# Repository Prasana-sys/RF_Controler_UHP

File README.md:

# RF_Controler_UHP

Controller Firmware - Contains STM32 code files

STM_RF_PCB - Contains PCB files

Documents - Documents used to build this project

old_RFST - old PCB design

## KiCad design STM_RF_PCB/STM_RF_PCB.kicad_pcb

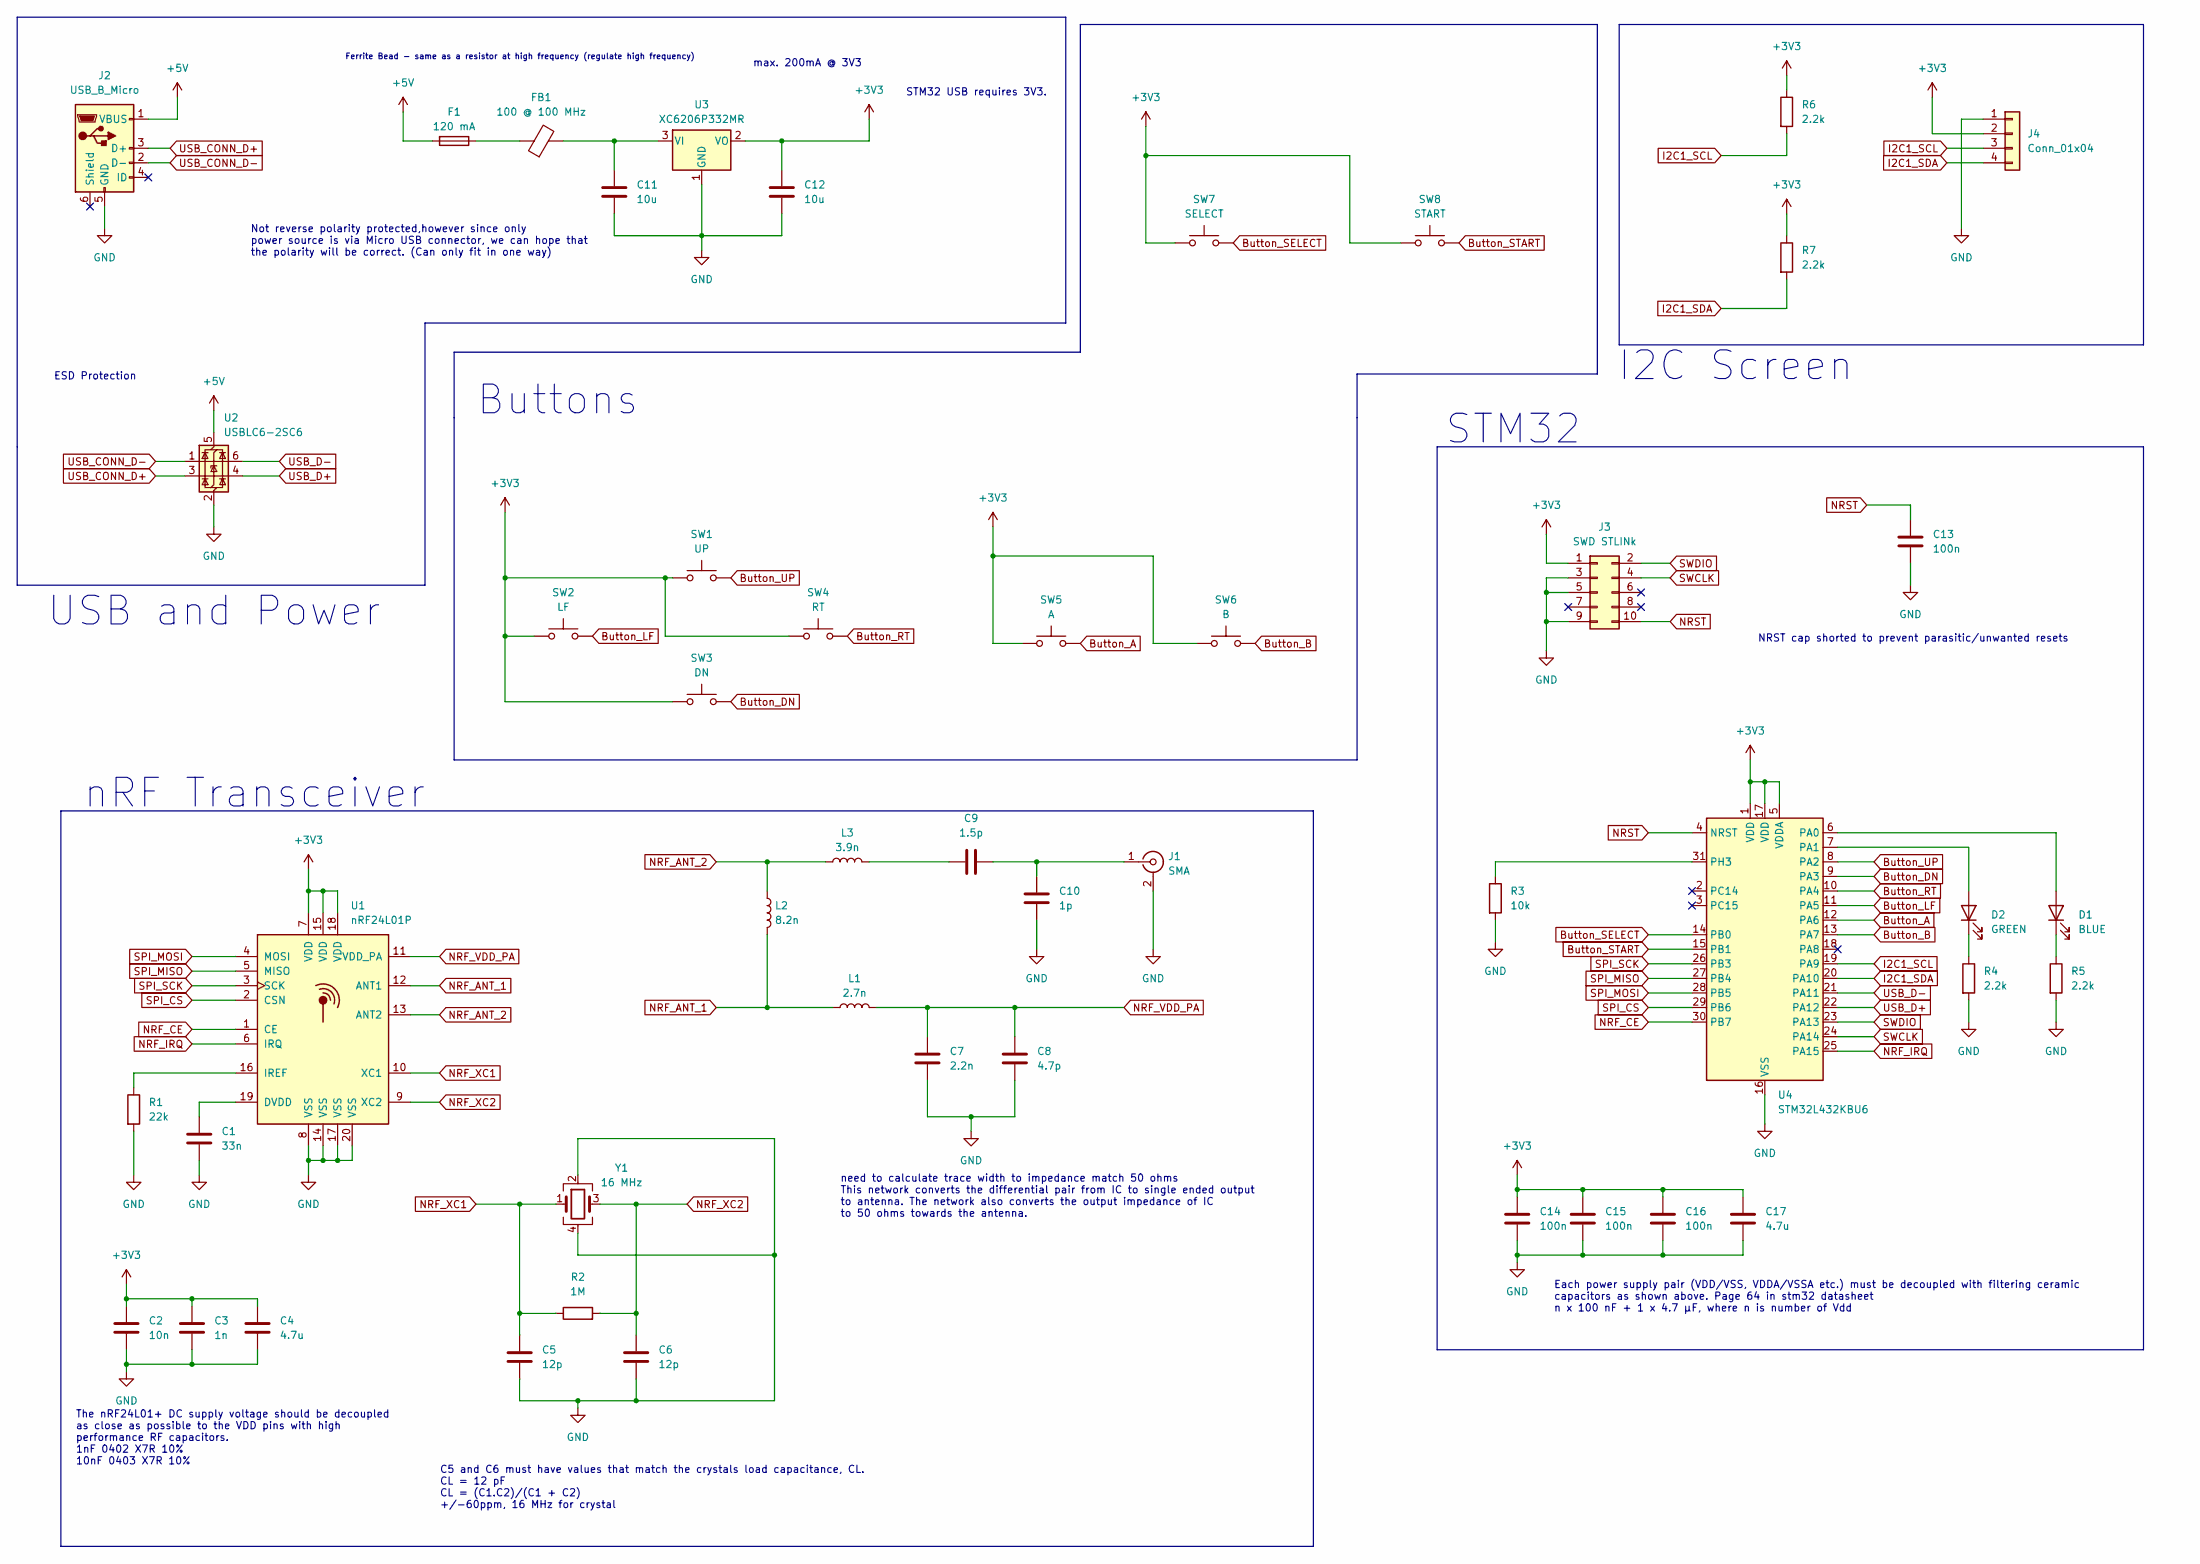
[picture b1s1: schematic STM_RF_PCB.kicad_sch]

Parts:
C1: 33n; C_0402_1005Metric; Part ID 0402F333M500NT
C2: 10n; R_0603_1608Metric; Part ID 0603B103K101NT
C3: 1n; C_0402_1005Metric; Part ID CC0402KRX7R7BB102
C4, C17: 4.7u; C_0603_1608Metric; Part ID CL10A475KP8NNNC
C5, C6: 12p; C_0402_1005Metric; Part ID 0402CG120J500NT
C7: 2.2n; C_0402_1005Metric; Part ID 0402B222K500NT
C8: 4.7p; C_0402_1005Metric; Part ID 0402CG4R7C500NT
C9: 1.5p; C_0402_1005Metric; Part ID 0402CG1R5C500NT
C10: 1p; C_0402_1005Metric; Part ID 0402CG1R0C500NT
C11, C12: 10u; C_0603_1608Metric; Part ID CL10A106KP8NNNC
C13, C14, C15, C16: 100n; C_0402_1005Metric; Part ID CL05B104KO5NNNC
D1: BLUE; LED_0603_1608Metric; Part ID 19-213/Y2C-CQ2R2L/3T(CY)
D2: GREEN; LED_0603_1608Metric; Part ID 19-217/GHC-YN1P2B18X/6T
F1: 120 mA; Fuse_1206_3216Metric; Part ID nSMD012
FB1: 100 @ 100 MHz; L_0805_2012Metric; Part ID GZ2012D101TF
J1: SMA; SMA-KWE902; Part ID SMA-KWE902
J2: USB_B_Micro; MICRO-02-G2P3-A1T2; Part ID MICRO-02-G2P3-A1T2
J3: SWD STLINk; PinHeader_2x05_P2.54mm_Vertical; Part ID HB-PH8-25425PB2GOP
J4: Conn_01x04; PinSocket_1x04_P2.54mm_Vertical; Part ID C2718488
L1: 2.7n; L_0402_1005Metric; Part ID SDCL1005C2N7STDF
L2: 8.2n; L_0402_1005Metric; Part ID SDCL1005C8N2JTDF
L3: 3.9n; L_0402_1005Metric; Part ID SDCL1005C3N9STDF
R1: 22k; R_0402_1005Metric; Part ID 0402WGF2202TCE
R2: 1M; R_0402_1005Metric; Part ID 0402WGF1004TCE
R3: 10k; R_0402_1005Metric; Part ID 0402WGF1002TCE
R4, R5, R6, R7: 2.2k; R_0603_1608Metric; Part ID 0603WAF2201T5E
SW1: UP; TC-1103-C-D; Part ID TC-1103-C-D
SW2: LF; TC-1103-C-D; Part ID TC-1103-C-D
SW3: DN; TC-1103-C-D; Part ID TC-1103-C-D
SW4: RT; TC-1103-C-D; Part ID TC-1103-C-D
SW5: A; TC-1103-C-D; Part ID TC-1103-C-D
SW6: B; TC-1103-C-D; Part ID TC-1103-C-D
SW7: SELECT; TC-1103-C-D; Part ID TC-1103-C-D
SW8: START; TC-1103-C-D; Part ID TC-1103-C-D
U1: nRF24L01P; QFN-20-1EP_4x4mm_P0.5mm_EP2.5x2.5mm
U2: USBLC6-2SC6; SOT-23-6
U3: XC6206P332MR
U4: STM32L432KBU6; Part ID C94784
Y1: 16 MHz; Crystal_SMD_3225-4Pin_3.2x2.5mm; Part ID X322516MLB4SI

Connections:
+3V3: C2.1, C3.1, C4.1, C12.1, C14.1, C15.1, C16.1, C17.1, J3.1, J4.2, R6.1, R7.1, SW1.1, SW2.1, SW3.1, SW4.1, SW5.1, SW6.1, SW7.1, SW8.1, U1.7 (VDD), U1.15 (VDD), U1.18 (VDD), U3.2 (VO), U4.1 (VDD), U4.5 (VDDA), U4.17 (VDD); also elsewhere on the board
+5V: F1.2, J2.1 (VBUS), U2.5 (VBUS)
Button_A: SW5.2, U4.12 (PA6)
Button_B: SW6.2, U4.13 (PA7)
Button_DN: SW3.2, U4.9 (PA3)
Button_LF: SW2.2, U4.11 (PA5)
Button_RT: SW4.2, U4.10 (PA4)
Button_SELECT: SW7.2, U4.14 (PB0)
Button_START: SW8.2, U4.15 (PB1)
Button_UP: SW1.2, U4.8 (PA2)
GND: C1.2, C2.2, C3.2, C4.2, C5.2, C6.2, C7.2, C8.2, C10.2, C11.2, C12.2, C13.2, C14.2, C15.2, C16.2, C17.2, J1.2 (Ext), J2.5 (GND), J3.3, J3.5, J3.9, J4.1, R1.2, R3.2, R4.2, R5.2, U1.8 (VSS), U1.14 (VSS), U1.17 (VSS), U1.20 (VSS), U2.2 (GND), U3.1 (GND), U4.16 (VSS), U4.32 (VSS), U4.33 (VSS), Y1.2, Y1.4; also elsewhere on the board
I2C1_SCL: J4.3, R6.2, U4.19 (PA9)
I2C1_SDA: J4.4, R7.2, U4.20 (PA10)
NRF_ANT_1: L1.1, L2.2, U1.12 (ANT1)
NRF_ANT_2: L2.1, L3.1, U1.13 (ANT2)
NRF_CE: U1.1 (CE), U4.30 (PB7)
NRF_IRQ: U1.6 (IRQ), U4.25 (PA15)
NRF_VDD_PA: C7.1, C8.1, L1.2, U1.11 (VDD_PA)
NRF_XC1: C5.1, R2.1, U1.10 (XC1), Y1.1
NRF_XC2: C6.1, R2.2, U1.9 (XC2), Y1.3
NRST: C13.1, J3.10, U4.4 (NRST)
unnamed: C9.1, L3.2
unnamed: D1.2 (A), U4.6 (PA0)
unnamed: D1.1 (K), R5.1
unnamed: D2.2 (A), U4.7 (PA1)
unnamed: D2.1 (K), R4.1
unnamed: F1.1, FB1.1
unnamed: C9.2, C10.1, J1.1 (In)
unnamed: C1.1, U1.19 (DVDD)
unnamed: R1.1, U1.16 (IREF)
unnamed: C11.1, FB1.2, U3.3 (VI)
unnamed: R3.1, U4.31 (PH3)
SPI_CS: U1.2 (CSN), U4.29 (PB6)
SPI_MISO: U1.5 (MISO), U4.27 (PB4)
SPI_MOSI: U1.4 (MOSI), U4.28 (PB5)
SPI_SCK: U1.3 (SCK), U4.26 (PB3)
SWCLK: J3.4, U4.24 (PA14)
SWDIO: J3.2, U4.23 (PA13)
USB_CONN_D+: J2.3 (D+), U2.3 (I/O2)
USB_CONN_D-: J2.2 (D-), U2.1 (I/O1)
USB_D+: U2.4 (I/O2), U4.22 (PA12)
USB_D-: U2.6 (I/O1), U4.21 (PA11)

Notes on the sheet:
I2C Screen
Buttons
NRST cap shorted to prevent parasitic/unwanted resets
need to calculate trace width to impedance match 50 ohms This network converts the differential pair from IC to single ended output to antenna. The network also converts the output impedance of IC to 50 ohms towards the antenna.
The nRF24L01+ DC supply voltage should be decoupled as close as possible to the VDD pins with high performance RF capacitors. 1nF 0402 X7R 10% 10nF 0403 X7R 10%
nRF Transceiver
STM32
Each power supply pair (VDD/VSS, VDDA/VSSA etc.) must be decoupled with filtering ceramic capacitors as shown above. Page 64 in stm32 datasheet n x 100 nF + 1 x 4.7 μF, where n is number of Vdd
ESD Protection
Not reverse polarity protected,however since only power source is via Micro USB connector, we can hope that the polarity will be correct. (Can only fit in one way)
C5 and C6 must have values that match the crystals load capacitance, CL. CL = 12 pF CL = (C1.C2)/(C1 + C2) +/-60ppm, 16 MHz for crystal
max. 200mA @ 3V3
STM32 USB requires 3V3.
USB and Power
Ferrite Bead - same as a resistor at high frequency (regulate high frequency)

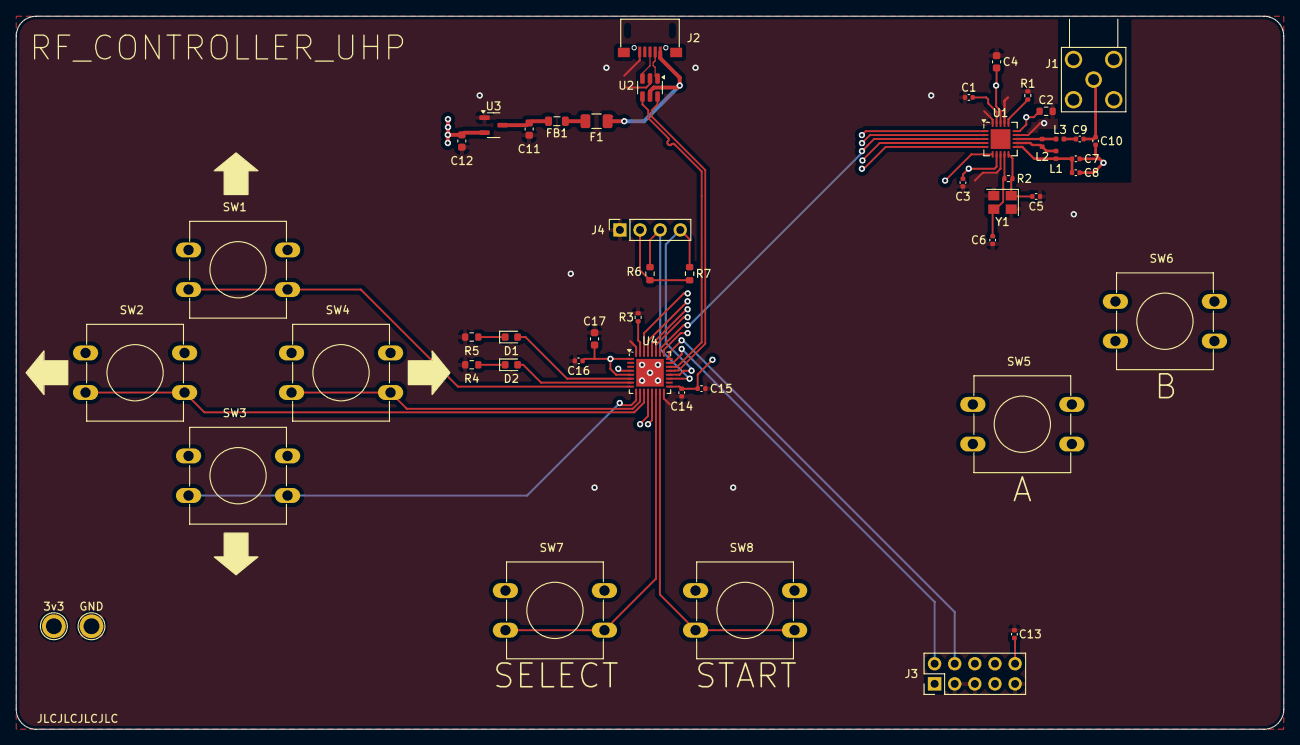
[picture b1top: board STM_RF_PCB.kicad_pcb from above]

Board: 4 copper layers, 160.0 x 90.0 mm, 50 parts (0 on the bottom side), 42 nets.

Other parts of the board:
3v3: TestPoint_Plated_Hole_D2.0mm
GND: TestPoint_Plated_Hole_D2.0mm

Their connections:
+3V3: 3v3.1; also elsewhere on the board
GND: GND.1; also elsewhere on the board

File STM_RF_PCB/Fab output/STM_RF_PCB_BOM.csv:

"Reference","Value","Datasheet","Footprint","Qty","DNP","Part ID"
"C1","33n","~","Capacitor_SMD:C_0402_1005Metric","1","","0402F333M500NT"
"C2","10n","~","Resistor_SMD:R_0603_1608Metric","1","","0603B103K101NT"
"C3","1n","~","Capacitor_SMD:C_0402_1005Metric","1","","CC0402KRX7R7BB102"
"C4,C17","4.7u","~","Capacitor_SMD:C_0603_1608Metric","2","","CL10A475KP8NNNC"
"C5,C6","12p","~","Capacitor_SMD:C_0402_1005Metric","2","","0402CG120J500NT"
"C7","2.2n","~","Capacitor_SMD:C_0402_1005Metric","1","","0402B222K500NT"
"C8","4.7p","~","Capacitor_SMD:C_0402_1005Metric","1","","0402CG4R7C500NT"
"C9","1.5p","~","Capacitor_SMD:C_0402_1005Metric","1","","0402CG1R5C500NT"
"C10","1p","~","Capacitor_SMD:C_0402_1005Metric","1","","0402CG1R0C500NT"
"C11,C12","10u","~","Capacitor_SMD:C_0603_1608Metric","2","","CL10A106KP8NNNC"
"C13,C14,C15,C16","100n","~","Capacitor_SMD:C_0402_1005Metric","4","","CL05B104KO5NNNC"
"D1","BLUE","~","LED_SMD:LED_0603_1608Metric","1","","19-213/Y2C-CQ2R2L/3T(CY)"
"D2","GREEN","~","LED_SMD:LED_0603_1608Metric","1","","19-217/GHC-YN1P2B18X/6T"
"F1","120 mA","~","Fuse:Fuse_1206_3216Metric","1","","nSMD012"
"FB1","100 @ 100 MHz","~","Inductor_SMD:L_0805_2012Metric","1","","GZ2012D101TF"
"J1","SMA"," ~","Library:SMA-KWE902","1","","SMA-KWE902"
"J2","USB_B_Micro","~","Library:MICRO-02-G2P3-A1T2","1","","MICRO-02-G2P3-A1T2"
"J3","SWD STLINk","~","Connector_PinHeader_2.54mm:PinHeader_2x05_P2.54mm_Vertical","1","","HB-PH8-25425PB2GOP"
"J4","Conn_01x04","~","Connector_PinSocket_2.54mm:PinSocket_1x04_P2.54mm_Vertical","1","","C2718488"
"L1","2.7n","~","Inductor_SMD:L_0402_1005Metric","1","","SDCL1005C2N7STDF"
"L2","8.2n","~","Inductor_SMD:L_0402_1005Metric","1","","SDCL1005C8N2JTDF"
"L3","3.9n","~","Inductor_SMD:L_0402_1005Metric","1","","SDCL1005C3N9STDF"
"R1","22k","~","Resistor_SMD:R_0402_1005Metric","1","","0402WGF2202TCE"
"R2","1M","~","Resistor_SMD:R_0402_1005Metric","1","","0402WGF1004TCE"
"R3","10k","~","Resistor_SMD:R_0402_1005Metric","1","","0402WGF1002TCE"
"R4,R5,R6,R7","2.2k","~","Resistor_SMD:R_0603_1608Metric","4","","0603WAF2201T5E"
"SW1","UP","~","Library:TC-1103-C-D","1","","TC-1103-C-D"
"SW2","LF","~","Library:TC-1103-C-D","1","","TC-1103-C-D"
"SW3","DN","~","Library:TC-1103-C-D","1","","TC-1103-C-D"
"SW4","RT","~","Library:TC-1103-C-D","1","","TC-1103-C-D"
"SW5","A","~","Library:TC-1103-C-D","1","","TC-1103-C-D"
"SW6","B","~","Library:TC-1103-C-D","1","","TC-1103-C-D"
"SW7","SELECT","~","Library:TC-1103-C-D","1","","TC-1103-C-D"
"SW8","START","~","Library:TC-1103-C-D","1","","TC-1103-C-D"
"U1","nRF24L01P","http://www.nordicsemi.com/eng/content/download/2726/34069/fi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","Package_DFN_QFN:QFN-20-1EP_4x4mm_P0.5mm_EP2.5x2.5mm","1","",""
"U2","USBLC6-2SC6","https://www.st.com/resource/en/datasheet/usblc6-2.pdf","Package_TO_SOT_SMD:SOT-23-6","1","",""
"U3","XC6206P332MR","https://www.torexsemi.com/file/xc6206/XC6206.pdf","Library:XC6206P332MR","1","",""
"U4","STM32L432KBU6","https://www.st.com/resource/en/datasheet/stm32l432kb.pdf","Library:STM32L432KBU6","1","","C94784"
"Y1","16 MHz","~","Crystal:Crystal_SMD_3225-4Pin_3.2x2.5mm","1","","X322516MLB4SI"

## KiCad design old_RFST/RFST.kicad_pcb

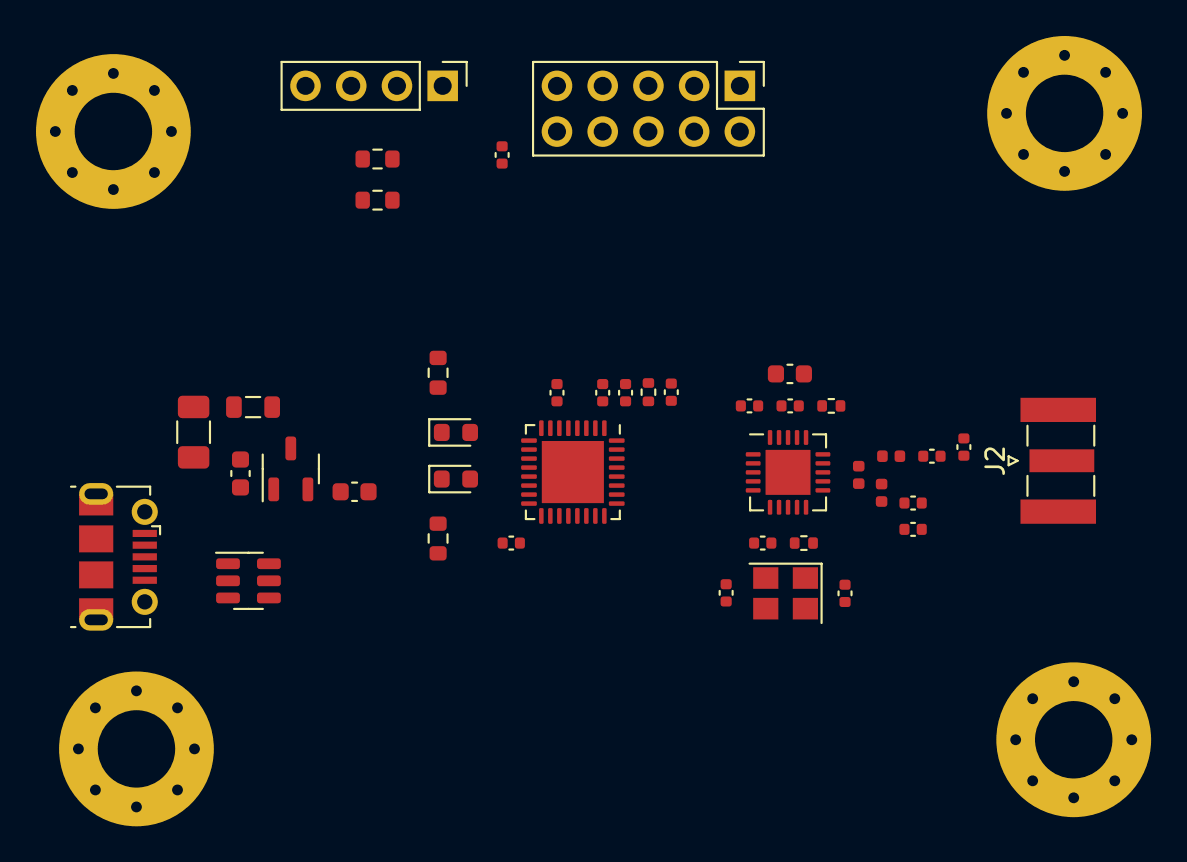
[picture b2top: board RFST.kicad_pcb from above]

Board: 2 copper layers, 45 parts (0 on the bottom side), 34 nets, no tracks yet.

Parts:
C1, C2, C8: 10u; C_0603_1608Metric
C3, C5, C6, C7: 100n; C_0402_1005Metric
C4: 1u; C_0402_1005Metric
C9, C10, C11: 10n; C_0402_1005Metric
C12: 33n; C_0402_1005Metric
C13, C14: 12p; C_0402_1005Metric
C15: 1p5; C_0402_1005Metric
C16: 1p; C_0402_1005Metric
C17: 2n2; C_0402_1005Metric
C18: 4p7; C_0402_1005Metric
D1: GREEN; LED_0603_1608Metric
D2: BLUE; LED_0603_1608Metric
F1: 100mA; Fuse_1206_3216Metric
FB1: 100 @ 100MHz; L_0805_2012Metric
H1, H2, H3, H4: MountingHole_Pad; MountingHole_4.3mm_M4_Pad_Via
J1: USB_B_Micro; USB_Micro-B_Molex-105017-0001
J2: SMA; SMA_Samtec_SMA-J-P-X-ST-EM1_EdgeMount
J3: 10 pin for stlink; PinHeader_2x05_P2.54mm_Vertical
J4: Conn_01x04; PinHeader_1x04_P2.54mm_Vertical
L1: 3n9; L_0402_1005Metric
L2: 8n2; L_0402_1005Metric
L3: 2n7; L_0402_1005Metric
R1: 10k; R_0402_1005Metric
R2, R3, R6, R7: 2k2; R_0603_1608Metric
R4: 22k; R_0402_1005Metric
R5: 1M; R_0402_1005Metric
U1: XC6206P332MR; SOT-23-3
U2: USBLC6-2SC6; SOT-23-6
U3: STM32L432KBUx; QFN-32-1EP_5x5mm_P0.5mm_EP3.45x3.45mm
U4: nRF24L01P; QFN-20-1EP_4x4mm_P0.5mm_EP2.5x2.5mm
Y1: 16MHz; Crystal_SMD_3225-4Pin_3.2x2.5mm

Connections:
+3V3: C2.1, C4.1, C5.1, C6.1, C7.1, C8.1, C9.1, C10.1, C11.1, J3.1, J4.3, R6.1, R7.1, U1.2 (VO), U3.1 (VDD), U3.5 (VDDA), U3.17 (VDD), U4.7 (VDD), U4.15 (VDD), U4.18 (VDD)
+5V: F1.1, J1.1 (VBUS), U2.5 (VBUS)
GND: C1.2, C2.2, C3.2, C4.2, C5.2, C6.2, C7.2, C8.2, C9.2, C10.2, C11.2, C12.2, C13.2, C14.2, C16.1, C17.1, C18.1, H1.1, H2.1, H3.1, H4.1, J1.5 (GND), J2.2 (Ext), J3.3, J3.5, J3.9, J4.4, R1.2, R2.2, R3.2, R4.2, U1.1 (GND), U2.2 (GND), U3.16 (VSS), U3.32 (VSS), U3.33 (VSS), U4.8 (VSS), U4.14 (VSS), U4.17 (VSS), U4.20 (VSS), Y1.2, Y1.4
I2C1_SCL: J4.2, R6.2, U3.19 (PA9)
I2C1_SDA: J4.1, R7.2, U3.20 (PA10)
NRF_ANT1: L2.2, L3.2, U4.12 (ANT1)
NRF_ANT2: L1.1, L2.1, U4.13 (ANT2)
NRF_CE: U3.30 (PB7), U4.1 (CE)
NRF_IRQ: U3.25 (PA15), U4.6 (IRQ)
NRF_VDD_PA: C17.2, C18.2, L3.1, U4.11 (VDD_PA)
NRF_XC1: C13.1, R5.2, U4.10 (XC1), Y1.1
NRF_XC2: C14.1, R5.1, U4.9 (XC2), Y1.3
NRST: C3.1, J3.10, U3.4 (NRST)
unnamed: C15.2, L1.2
unnamed: D1.2 (A), U3.9 (PA3)
unnamed: D1.1 (K), R2.1
unnamed: D2.2 (A), U3.8 (PA2)
unnamed: D2.1 (K), R3.1
unnamed: F1.2, FB1.1
unnamed: C15.1, C16.2, J2.1 (In)
unnamed: C1.1, FB1.2, U1.3 (VI)
unnamed: R1.1, U3.31 (PH3)
unnamed: C12.1, U4.19 (DVDD)
unnamed: R4.1, U4.16 (IREF)
SPI3_CS: U3.29 (PB6), U4.2 (CSN)
SPI3_MISO: U3.27 (PB4), U4.5 (MISO)
SPI3_MOSI: U3.28 (PB5), U4.4 (MOSI)
SPI3_SCK: U3.26 (PB3), U4.3 (SCK)
SWCLK: J3.4, U3.24 (PA14)
SWDIO: J3.2, U3.23 (PA13)
USB_CONN_D+: J1.3 (D+), U2.6 (IO1)
USB_CONN_D-: J1.2 (D-), U2.4 (IO2)
USB_D+: U2.1 (IO1), U3.22 (PA12)
USB_D-: U2.3 (IO2), U3.21 (PA11)

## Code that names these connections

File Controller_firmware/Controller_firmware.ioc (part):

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Mcu.Name=STM32L432K(B-C)Ux
Mcu.Package=UFQFPN32
Mcu.UserName=STM32L432KBUx
PA0.GPIOParameters=GPIO_Label
PA0.GPIO_Label=blue
PA0.Signal=GPIO_Output
PA1.GPIOParameters=GPIO_Label
PA1.GPIO_Label=green
PA1.Signal=GPIO_Output
PA10.Mode=I2C
PA10.Signal=I2C1_SDA
PA11.Mode=Device
PA11.Signal=USB_DM
PA12.Mode=Device
PA12.Signal=USB_DP
PA13\ (JTMS-SWDIO).Mode=Serial_Wire
PA13\ (JTMS-SWDIO).Signal=SYS_JTMS-SWDIO
PA14\ (JTCK-SWCLK).Mode=Serial_Wire
PA14\ (JTCK-SWCLK).Signal=SYS_JTCK-SWCLK
PA15\ (JTDI).Signal=GPIO_Input
PA2.Signal=GPXTI2
PA3.Signal=GPXTI3
PA4.Signal=GPXTI4
PA5.Signal=GPXTI5
PA6.Signal=GPXTI6
PA7.Signal=GPXTI7
PA9.Mode=I2C
PA9.Signal=I2C1_SCL
PB0.Signal=GPXTI0
PB1.Signal=GPXTI1
PB3\ (JTDO-TRACESWO).Mode=Full_Duplex_Master
PB3\ (JTDO-TRACESWO).Signal=SPI1_SCK
PB4\ (NJTRST).Mode=Full_Duplex_Master
PB4\ (NJTRST).Signal=SPI1_MISO
PB5.Mode=Full_Duplex_Master
PB5.Signal=SPI1_MOSI
PB6.Signal=GPIO_Output
RCC.HSE_VALUE=8000000
RCC.SYSCLKFreq_VALUE=80000000
RCC.SYSCLKSource=RCC_SYSCLKSOURCE_PLLCLK
board=custom

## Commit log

2024-02-06 Initial commit for HW development
2024-02-06 Create LICENSE
2024-02-06 Update LICENSE
2024-02-26 Added design spec
2024-02-26 Added gitignore
2024-03-18 Update 3/18
2024-05-20 Added new project with buttons in schematic
2024-05-20 Added I2C interface back and changed to SMA antenna
2024-05-20 Adding footprint for micro usb
2024-05-21 Schematic Symbols update for KiCad 8.0, updated footprint for Micro USB, added 3d model to footprint
2024-05-22 Added part IDs, footprints for all in Power Management
2024-05-22 Added footprints and Part ID for I2C Screen
2024-05-23 Small fixes
2024-05-23 Footprints, part ID for RF block except SMA
2024-05-24 Footprint and Part ID for SMA antenna
2024-05-28 STM32 block footprints, Part IDs
2024-05-29 Buttons block, footprint and part ID
2024-05-29 Work on PCB
2024-05-31 Added start select buttons
2024-05-31 PCB work
2024-06-07 PCB work complete + fab outputs
2024-06-07 FAB ouput zipfile
2024-06-07 Removed fab outputs plus fixed trace impednances
2024-06-08 added san jose 2024
2024-06-09 Fab outputs
2025-03-11 Controller Firmware
